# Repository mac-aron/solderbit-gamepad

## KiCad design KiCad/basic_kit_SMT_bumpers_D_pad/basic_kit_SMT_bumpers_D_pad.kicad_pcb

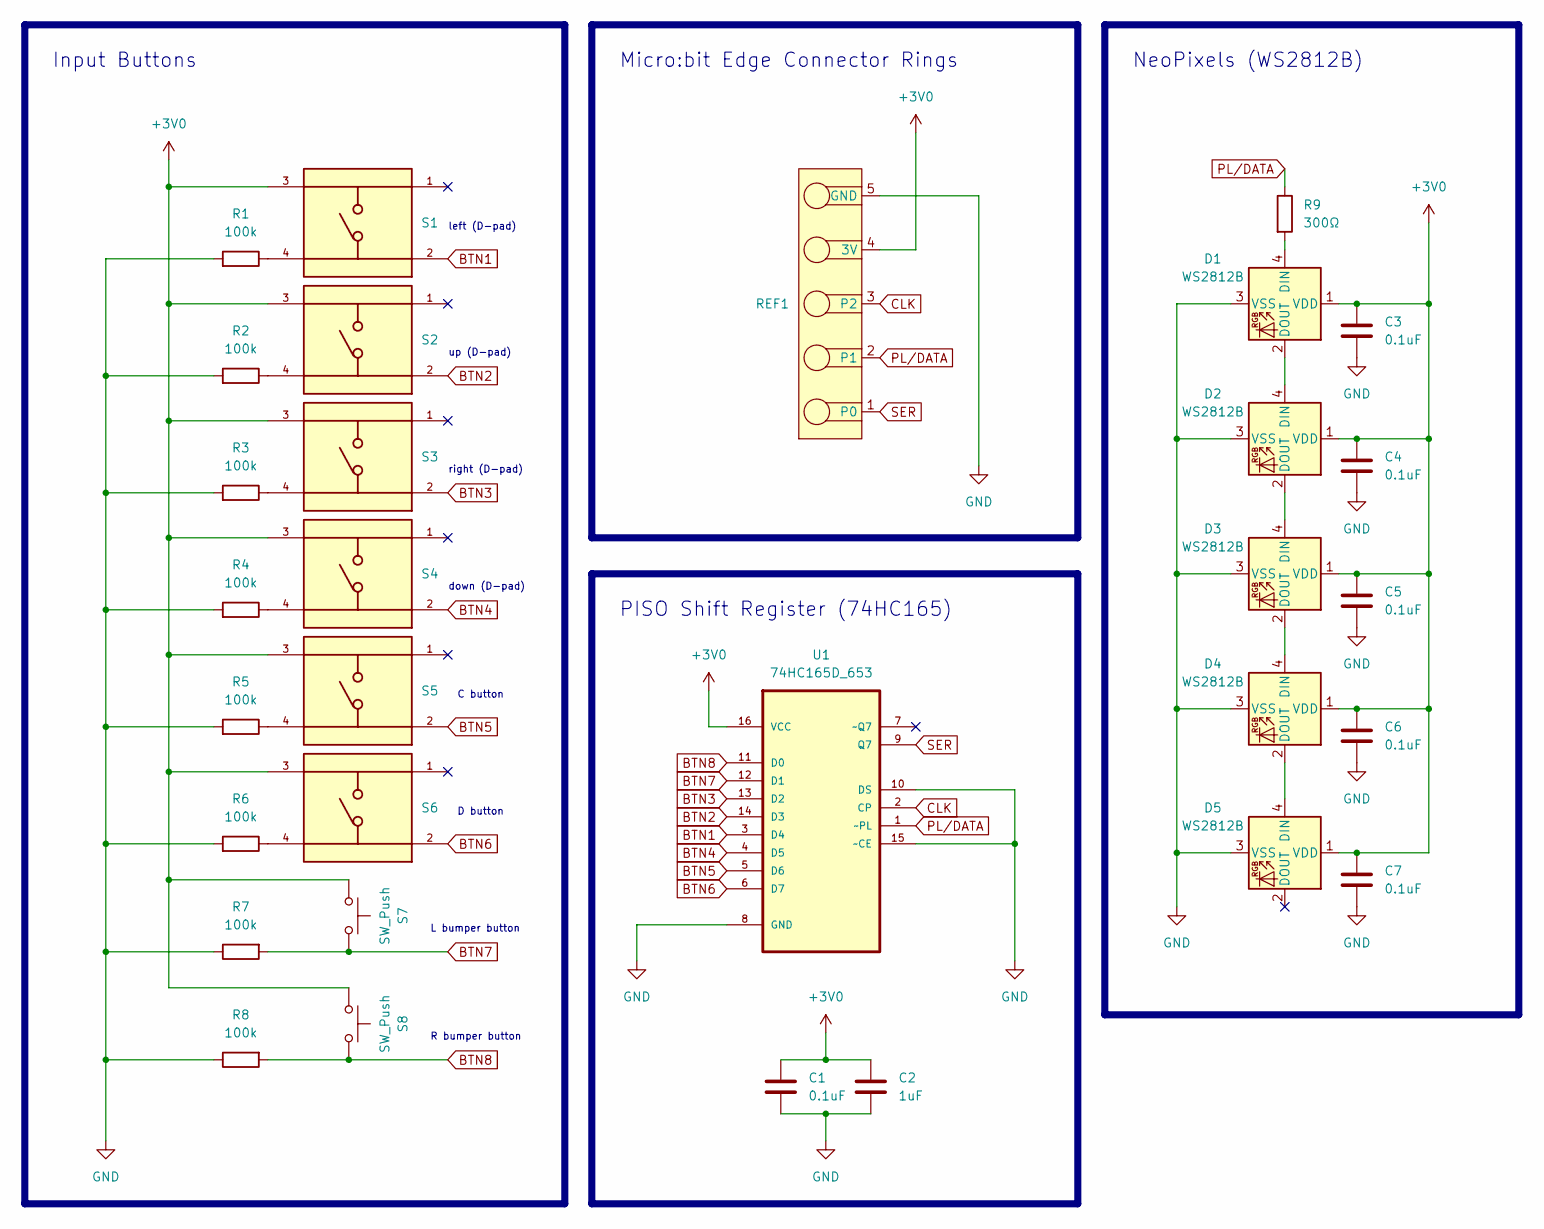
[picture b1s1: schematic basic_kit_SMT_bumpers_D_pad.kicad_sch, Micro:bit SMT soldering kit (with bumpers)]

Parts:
C1, C3, C4, C5, C6, C7: 0.1uF; C_1206_3216Metric_Pad1.33x1.80mm_HandSolder
C2: 1uF; C_1206_3216Metric_Pad1.33x1.80mm_HandSolder
D1, D2, D3, D4, D5: WS2812B; LED_WS2812B_PLCC4_5.0x5.0mm_P3.2mm
R1, R2, R3, R4, R5, R6, R7, R8: 100k; R_1206_3216Metric_Pad1.30x1.75mm_HandSolder
R9: 300Ω; R_1206_3216Metric_Pad1.30x1.75mm_HandSolder
REF1: Edge_Connector_Rings
S1, S2, S3, S4, S5, S6: TS04-66-95-BK-100-SMT; SW_TS04-66-95-BK-100-SMT; PARTREV 1.0
S7, S8: SW_Push; TS-1037_right_angle
U1: 74HC165D_653; SOIC127P600X175-16N; MPN 74HC165D,653

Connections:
+3V0: C1.2, C2.2, C3.1, C4.1, C5.1, C6.1, C7.1, D1.1 (VDD), D2.1 (VDD), D3.1 (VDD), D4.1 (VDD), D5.1 (VDD), REF1.4 (3V), S1.3, S2.3, S3.3, S4.3, S5.3, S6.3, S7.1, S8.1, U1.16 (VCC)
BTN1: S1.2, U1.3 (D4)
BTN2: S2.2, U1.14 (D3)
BTN3: S3.2, U1.13 (D2)
BTN4: S4.2, U1.4 (D5)
BTN5: S5.2, U1.5 (D6)
BTN6: S6.2, U1.6 (D7)
BTN7: R7.2, S7.2, U1.12 (D1)
BTN8: R8.2, S8.2, U1.11 (D0)
CLK: REF1.3 (P2), U1.2 (CP)
GND: C1.1, C2.1, C3.2, C4.2, C5.2, C6.2, C7.2, D1.3 (VSS), D2.3 (VSS), D3.3 (VSS), D4.3 (VSS), D5.3 (VSS), R1.2, R2.2, R3.2, R4.2, R5.2, R6.2, R7.1, R8.1, REF1.5 (GND), U1.8 (GND), U1.10 (DS), U1.15 (~CE)
unnamed: D1.4 (DIN), R9.2
unnamed: D1.2 (DOUT), D2.4 (DIN)
unnamed: D2.2 (DOUT), D3.4 (DIN)
unnamed: D3.2 (DOUT), D4.4 (DIN)
unnamed: D4.2 (DOUT), D5.4 (DIN)
unnamed: R1.1, S1.4
unnamed: R2.1, S2.4
unnamed: R3.1, S3.4
unnamed: R4.1, S4.4
unnamed: R5.1, S5.4
unnamed: R6.1, S6.4
PL/DATA: R9.1, REF1.2 (P1), U1.1 (~PL)
SER: REF1.1 (P0), U1.9 (Q7)

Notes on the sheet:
D button
down (D-pad)
NeoPixels (WS2812B)
C button
Input Buttons
L bumper button
left (D-pad)
R bumper button
Micro:bit Edge Connector Rings
right (D-pad)
up (D-pad)
PISO Shift Register (74HC165)

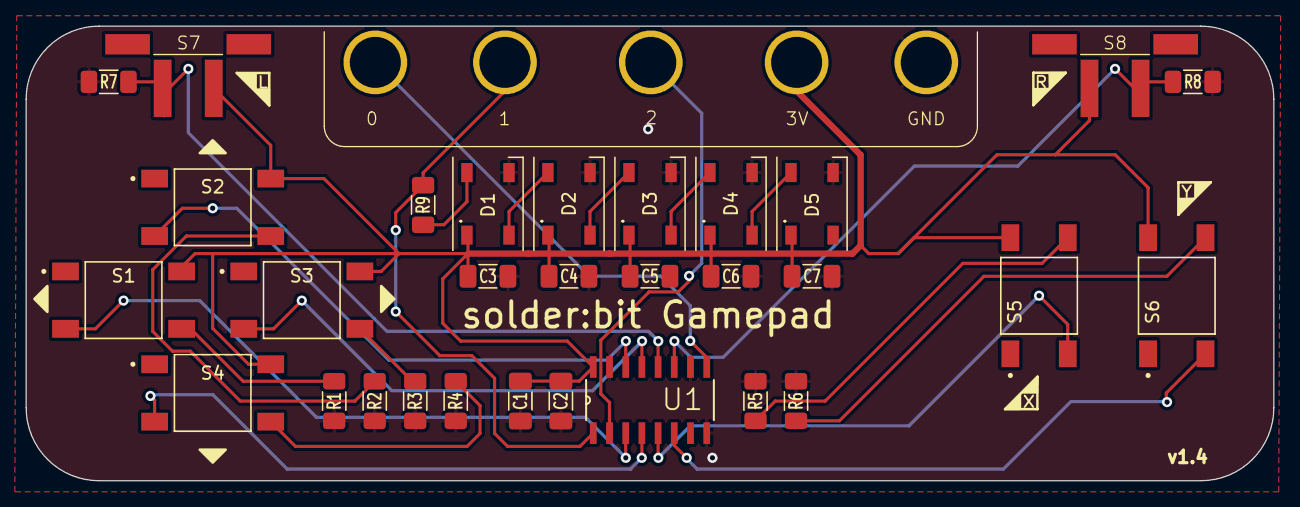
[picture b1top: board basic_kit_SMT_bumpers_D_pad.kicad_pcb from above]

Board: 2 copper layers, 97.8 x 35.6 mm, 32 parts (1 on the bottom side), 24 nets.

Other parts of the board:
Ref**: Val**; Lancaster_Cityscape

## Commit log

2024-05-29 Renamed directories"
